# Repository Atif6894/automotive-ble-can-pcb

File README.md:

# Automotive BLE-to-CAN Communication Module

A small 4-layer board that sits on a vehicle's 12/24 V harness, talks CAN FD through a TCAN4550-Q1, and exposes it over Bluetooth LE through a CC2340R5-Q1. It runs from 9–36 V vehicle power with reverse-battery and load-dump protection, and rides through power loss on a 1S Li-ion backup cell. This is a **pre-fabrication design**: schematic, layout and manufacturing outputs are complete and pass KiCad ERC/DRC, but no board has been built or measured yet.

| Area | Implementation |
|------|----------------|
| MCU | TI CC2340R5-Q1 (CC2340R52E0WRHBRQ1, BLE 5.3, QFN32) |
| CAN | TI TCAN4550-Q1 (CAN FD controller + transceiver) |
| Vehicle input | 9–36 V, fused, TVS-clamped, ideal-diode reverse protection |
| Intermediate rail | 6.0 V (LM5164-Q1 buck) |
| Digital rail | 3.3 V (TPS62A01-Q1), shared by MCU and TCAN VIO |
| CAN interface | CAN / CAN FD, optional split 120 Ω termination |
| MCU ↔ CAN | SPI + nINT / RST / nWKRQ |
| Backup power | 1S Li-ion connector, BQ24074 charger / power path |
| RF | TI SWRU120D inverted-F PCB antenna, U.FL conducted-test option |
| Debug | 10-pin Cortex SWD + 28 test points |
| PCB | 80 × 60 mm, 4 layers, 1.6 mm, single-sided assembly |
| EDA | KiCad 10 |

## PCB Preview

Full schematic: [schematic/schematic.pdf](schematic/schematic.pdf) · all copper layers: [schematic/pcb_layers.pdf](schematic/pcb_layers.pdf)

---

## Overview

The brief was a module that connects to a vehicle CAN bus and makes it reachable over BLE. The requirements that drove the design:

- 9–36 V vehicle input (12 V and 24 V systems), surviving reverse battery and a centrally suppressed load dump
- CAN / CAN FD using the TCAN4550, with bus protection and a termination strategy
- BLE using a CC2340-family automotive part
- A backup battery so the MCU and radio stay alive through crank and brief power loss
- SPI between the BLE MCU and the CAN controller
- Programming/debug access and test access for bring-up and production
- A layout that is DRC-clean and ready to send to a 4-layer fab

## My Role

This was my project end to end at the design-package level: system architecture, part selection against datasheets, the six-sheet hierarchical schematic, PCB placement/routing and stackup choice, test and debug access, BOM, DFMEA, power budget, validation plan, and the Gerber/drill/assembly outputs. I used AI-assisted tooling during development (including scripted generation of parts of the KiCad schematic and the routing); I directed and reviewed that work against the datasheets and the KiCad checks, and I'm responsible for the design decisions described here.

## System Architecture

Power comes in on J1 (Molex Micro-Fit 3.0, 2×3), which also carries CANH/CANL and an ignition line. The vehicle supply goes fuse → TVS → ideal diode → 6.0 V buck. The 6.0 V rail feeds the TCAN4550's VSUP directly and also feeds the BQ24074 power-path charger; the charger's output (vehicle-derived or from the battery) feeds a 3.3 V buck that powers the CC2340 and the TCAN4550's logic I/O. The CC2340 talks to the TCAN4550 over SPI0 plus interrupt, reset and wake lines. The antenna is at the top-left board edge, the vehicle connector at the bottom-right.

## Power Architecture

```
J1 VBAT 9–36 V
 └─ F1 1 A fuse ─ D1 SMDJ36CA TVS ─ U1 LM74700-Q1 + Q1 BUK7Y41-80E (ideal diode)
     └─ VIN_PROT (33 µF/50 V bulk)
         └─ U2 LM5164-Q1 buck, ~300 kHz, UVLO 7.5 V / 7.0 V ──► V6P0 = 6.0 V
             ├─ FB1 ─► TCAN4550 VSUP
             └─ U3 BQ24074 IN ──► VBATSYS (4.4 V, or battery) ◄─► J3 1S Li-ion
                   └─ U4 TPS62A01-Q1 ──► +3V3 (3.32 V) ─► CC2340 VDDS, TCAN VIO
```

- **Reverse polarity:** an LM74700-Q1 driving an 80 V N-FET instead of a series Schottky. It blocks a reversed battery (to −36 V) without the ~0.5 V forward drop and heat of a diode. I picked the BUK7Y41-80E (standard-level) over the logic-level BUK9Y41 because the logic-level part's V<sub>GS</sub> rating doesn't cover the controller's gate drive.
- **Transients:** the SMDJ36CA (V<sub>RWM</sub> 36 V, V<sub>C</sub> ≤ 58.1 V) sits right after the fuse. The design assumes the vehicle has central load-dump suppression (ISO 16750-2 test B), so the clamped node stays inside the LM74700 (65 V abs), FET (80 V) and LM5164 (100 V) ratings.
- **Buck:** the LM5164-Q1 handles the full input range with margin; its UVLO divider (7.5 V rising / 7.0 V falling) cleanly hands over to the battery during cranking instead of letting the rail droop.
- **High-voltage nets** (VIN_RAW/FUSED/PROT, SW, gate) are in their own net class with 0.3 mm clearance.

Full set-point math, load budget and calculated thermal numbers are in [documentation/POWER_BUDGET.md](documentation/POWER_BUDGET.md).

## CAN / CAN FD

- **TCAN4550-Q1** integrates the CAN FD controller and transceiver, so the CC2340 (which has no CAN peripheral) only needs SPI: SCLK DIO8, CSN DIO11, POCI DIO12, PICO DIO13, plus nINT (DIO14), RST (DIO18), nWKRQ (DIO19).
- **Clock:** 40 MHz crystal with 100 Ω series on OSC1.
- **Bus protection** at the connector: PESD2CAN ESD diode, then a TDK ACT45B common-mode choke, then 47 pF line caps, then 0 Ω links (R40/R41) that can be swapped for series damping.
- **Termination:** split termination, 2 × 60.4 Ω with a 4.7 nF midpoint cap to GND, connected through solder jumpers JP1/JP2. Default open, because a plug-in module is usually a bus *tap*, not an end node. Closing both jumpers makes it a 120 Ω end node on the bench. The silkscreen says so next to the jumpers.
- **Wake:** ignition line into WAKE through the TCAN datasheet's 33 k / 3 k / 10 nF network; INH has a 100 k pull-down.
- **nWKRQ:** this pin defaults to the TCAN's internal 3.6 V rail, which is above the CC2340's 3.3 V I/O. A 1 k series resistor limits current into the MCU pin until firmware switches nWKRQ to VIO (register 0x0800 bit 19).

## BLE / MCU

- **Part:** CC2340R52E0WRHBRQ1 (CC2340R5-Q1, AEC-Q100). The brief named "CC2340R40", which I couldn't find in TI's documentation, so I used the closest automotive family member and flagged it.
- **Clocks:** 48 MHz crystal (TZ3908AAAO43, the part TI validates) and 32.768 kHz crystal for sleep timing.
- **Supply:** 100 nF per VDDS pin, internal DC/DC with 10 µH + 10 µF on VDDR as TI requires, 1 µF on VDDD.
- **RF:** LPF → DC block → π-match → 0.40 mm 50 Ω microstrip → TI SWRU120D inverted-F antenna at the board edge, with a copper keep-out on all four layers. Matching values are TI reference starting values, not tuned.
- **Debug:** SWDIO DIO16, SWDCK DIO17, nRESET to the SWD header.

## Backup Battery

J3 is a keyed JST PH 3-pin (BAT+, NTC, GND) for a protected 1S Li-ion pack with a 10 k NTC. The BQ24074 charges at 100 mA (R<sub>ISET</sub> 8.87 k) with a ~0.5 A input limit, and its power-path output switches from the 6.0 V input to the battery when vehicle power drops. Intended behavior during crank or power loss: the CC2340 and radio stay up on the battery, the TCAN4550 loses VSUP and has to be re-initialized by firmware when power returns. That behavior is designed from the datasheets, **not** tested.

## PCB Layout

| Top 3D | Bottom 3D |
|---|---|
|  |  |

| L1 F.Cu | L2 In1 (GND) | L3 In2 | L4 B.Cu |
|---|---|---|---|
|  |  |  |  |

- **Stackup:** F.Cu signals + RF / In1 solid GND / In2 signals + power / B.Cu routing, GND pours on all layers. Assumes a JLC04161H-7628 style stackup (0.21 mm prepreg to In1), which sets the 0.40 mm microstrip width. Details: [documentation/STACKUP_AND_LAYOUT.md](documentation/STACKUP_AND_LAYOUT.md).
- **Zoning:** antenna top-left with keep-out; CC2340 just below it with the RF chain in a straight line to the feed; power input on the right edge (fuse, TVS, ideal diode in a row) with the buck top-right and a tight CIN–U2–L1–COUT loop; vehicle connector J1 bottom-right with CAN ESD and CMC directly next to it; TCAN4550 between J1 and the MCU to keep SPI short; battery connector bottom-left, away from the antenna.
- **Ground:** every GND pad gets a via to In1, via arrays under the thermal pads, four plated M3 holes tied to GND.
- **Assembly:** all parts on the top side, 3 fiducials, single reflow pass.

## Design Highlight: one 6.0 V rail doing three jobs

**Problem.** The TCAN4550 needs VSUP ≥ 5.5 V. Its internal LDO burns (VSUP − 5 V) × ~80 mA whenever the bus is driven, so feeding it straight from a 24–36 V vehicle input would dissipate a lot of heat in a small QFN (the datasheet's thermal-shutdown example is at 20 V). Meanwhile, the BLE side needs a battery-backed 3.3 V rail, and the charger that provides it has its own input window (BQ24074 OVP at 10.5 V).

**Obvious alternatives.** Run VSUP from the protected vehicle rail (simple, hot at 24 V+), or build a 5 V rail (below TCAN's 5.5 V minimum), or add a separate rail for the charger.

**What I did.** One LM5164 buck set to 6.0 V (1.2 V × (1 + 200 k / 49.9 k) = 6.01 V). That single number satisfies three constraints at once:

1. above TCAN VSUP minimum (5.5 V) with margin for tolerance and the FB1 ferrite drop,
2. low enough that the TCAN's internal LDO dissipates roughly 1 V × load rather than 20–30 V × load,
3. inside the BQ24074's input range, so the same rail also feeds the charger/power path, which then makes the 3.3 V rail for the MCU **and** the TCAN VIO pin.

**Payoff.** Both chips share one 3.3 V logic domain, so SPI/interrupt/reset need no level shifters. The CAN transceiver's heat is decoupled from the vehicle voltage. The battery path only has to back up the low-power 3.3 V domain, while the power-hungry CAN supply simply drops out during a crank and gets re-initialized, which is fine for a bus tap. It's one regulator and two resistors, instead of a 5 V rail plus a separate charger supply plus level translation.

A smaller detail in the same spirit: the IFA antenna's two grounded shorting tabs are connected through 0 Ω links (R67/R68), and the feed has a 0 Ω steering pair (R65 fitted / R66 DNP) to a U.FL connector. That makes the antenna's DC short and the conducted-RF path reconfigurable with a soldering iron during RF tuning, without a board respin.

## Design Verification (in KiCad, not on hardware)

Run with KiCad 10.0.6 `kicad-cli` on the delivered files ([reports](manufacturing/reports/)):

- **ERC:** 0 errors, 0 warnings.
- **DRC:** 0 errors, 0 unconnected items, 0 schematic-parity issues. 45 warnings remain:
  - 23 `via_dangling`: vias connected on only one layer (including some on signal nets such as SPI_nCS, nRESET, X32P, VBATSYS left over from routing). They don't break connectivity but should be cleaned up before fab.
  - 2 `hole_to_hole`: these are routing vias, not mounting holes or intentional mechanical features. Two GND vias at (52.5, 60.1) / (52.6, 59.8) mm have only 0.078 mm drill-to-drill spacing, and two TCAN_GPO2 vias at (56.8, 75.0) / (57.2, 75.1) mm have 0.193 mm, against a 0.2 mm rule. Each pair is on the same net, so there's no electrical short, but the 0.078 mm pair is a real fabrication risk (drill breakout). **Fix before ordering** by deleting or moving one via of each pair.
  - 20 silkscreen overlap / silk-over-copper from stock footprint outlines.
- The copper-zone fill saved in the board file was stale: run without refilling zones, DRC flags two IGN_RAW tracks touching the B.Cu GND pour. I refilled the zones (no tracks, footprints or nets changed), re-ran DRC, and regenerated the Gerbers, drill and assembly outputs from the refilled board, so the fab files match the clean DRC result.
- Symbol-pin vs footprint-pad check and BOM-vs-netlist cross-check (all references match).
- Pinouts and key values traced to datasheets: [documentation/DATASHEET_TRACE.md](documentation/DATASHEET_TRACE.md).

## Manufacturing Outputs

| File | Content |
|---|---|
| [manufacturing/gerbers.zip](manufacturing/gerbers.zip) | 4 copper layers, mask, paste, silkscreen, edge cuts, Gerber job file |
| [manufacturing/drill_files.zip](manufacturing/drill_files.zip) | Excellon drill + drill map |
| [bytebeam_pos_front.csv](manufacturing/assembly_outputs/bytebeam_pos_front.csv) | pick-and-place (top side) |
| [bytebeam.d356](manufacturing/assembly_outputs/bytebeam.d356) | IPC-D-356 netlist for bare-board test |
| [bytebeam_ipc2581.xml](manufacturing/assembly_outputs/bytebeam_ipc2581.xml) | IPC-2581 |
| [bytebeam_netlist.xml](manufacturing/assembly_outputs/bytebeam_netlist.xml) | KiCad netlist |
| [bytebeam.step](manufacturing/assembly_outputs/bytebeam.step) | 3D STEP model (a few connector/fuse 3D models were missing at export) |
| [documentation/BOM.csv](documentation/BOM.csv) | BOM with MPN, ratings, AEC qualification, alternatives, open assumptions |
| [schematic/assembly_top.pdf](schematic/assembly_top.pdf) | top assembly drawing |

## Debug / Bring-Up Considerations

I laid out the test access in the order I'd bring the board up:

1. **Power, stage by stage, with a current-limited supply.** Test points on every rail along the chain: VIN_RAW (TP1) → VIN_FUSED (TP2) → VIN_PROT (TP3) → V6P0 (TP4/TP25) → VBAT (TP5) / VBATSYS (TP6) → +3V3 (TP8/TP19), plus BQ_PGOOD (TP26) and BQ_nCHG (TP7). If a rail is missing, the fault is between two adjacent test points. Five GND test points spread over the board for scope grounds.
2. **MCU alive.** 10-pin Cortex SWD header (J2) for an XDS110/J-Link, and SWDIO/SWDCK/nRESET are also on test pads (TP16/TP17/TP15) for a pogo-pin fixture in production. A blinky LED is on a DIO.
3. **SPI to the TCAN.** SCLK, MOSI, MISO, nCS, nINT and TCAN_RST all on test points (TP21/22/12/23/20/24), so a logic analyzer can decode the first device-ID read (registers 0x0000–0x0003) without probing a 0.5 mm QFN.
4. **CAN.** CANH/CANL test points (TP9/TP10), TCAN_INH (TP11), and the termination jumpers so the board can be an end node on a two-node bench bus.
5. **RF.** Fit R66 / remove R65 to route the radio to the U.FL connector (J4) for conducted power and harmonics on a spectrum analyzer, then reverse it for antenna S11 on a VNA.

Full step-by-step plan: [documentation/VALIDATION_PLAN.md](documentation/VALIDATION_PLAN.md).

## What Still Needs Physical Validation

Nothing has been fabricated, powered or measured. All of the following are open:

- Fix the two `hole_to_hole` via pairs and clean up the dangling vias before fab
- RF matching network tuning (values are TI reference starting points; topology needs confirming against the LP-EM-CC2340R5-Q1 design files)
- Antenna performance on this stackup and in an enclosure (S11, efficiency, range)
- 50 Ω microstrip impedance with the fab's real dielectric data
- Crystal load values (TCAN 40 MHz caps are assumptions)
- EMC/EMI (CISPR 25; the 300 kHz buck lands in the AM band), ESD (IEC 61000-4-2 / ISO 10605)
- Transients: ISO 7637-2 pulses, ISO 16750-2 load dump, reverse battery, cranking profile
- Thermal performance (current numbers are datasheet θ<sub>JA</sub> estimates)
- CAN signal integrity and FD bit timing (CANH/CANL are routed as two nets, not a coupled pair)
- Battery charging, power-path handover and sleep current
- Land patterns for Coilcraft XGL inductors and the 48 MHz crystal against vendor drawings
- BQ24074 is not AEC-Q100 qualified; an automotive-qualified charger would be needed for production
- Board bring-up and firmware

Design risks and mitigations are tracked in the [DFMEA](documentation/DFMEA.csv) (33 failure modes).

## Design Files

- Schematic: [schematic/schematic.pdf](schematic/schematic.pdf) and per-sheet images in [images/](images/)
- PCB layer plots: [schematic/pcb_layers.pdf](schematic/pcb_layers.pdf)
- KiCad project: [design_files/](design_files/) (open `bytebeam_ble_can.kicad_pro` in KiCad 10; custom symbols/footprints in `design_files/lib/`)
- BOM: [documentation/BOM.csv](documentation/BOM.csv)
- DFMEA: [documentation/DFMEA.csv](documentation/DFMEA.csv)
- Power budget: [documentation/POWER_BUDGET.md](documentation/POWER_BUDGET.md)
- Stackup and layout notes: [documentation/STACKUP_AND_LAYOUT.md](documentation/STACKUP_AND_LAYOUT.md)
- Validation plan: [documentation/VALIDATION_PLAN.md](documentation/VALIDATION_PLAN.md)
- Manufacturing outputs: [manufacturing/](manufacturing/)

Originally done as a hardware design assignment for Bytebeam; the board silkscreen still carries that name.

## Tools and Skills

KiCad 10 (schematic capture, 4-layer PCB layout, DRC/ERC, fab outputs) · automotive power electronics (protection, buck regulation, power path) · CAN / CAN FD · SPI · BLE · RF layout · DFMEA · Python for calculations and output generation

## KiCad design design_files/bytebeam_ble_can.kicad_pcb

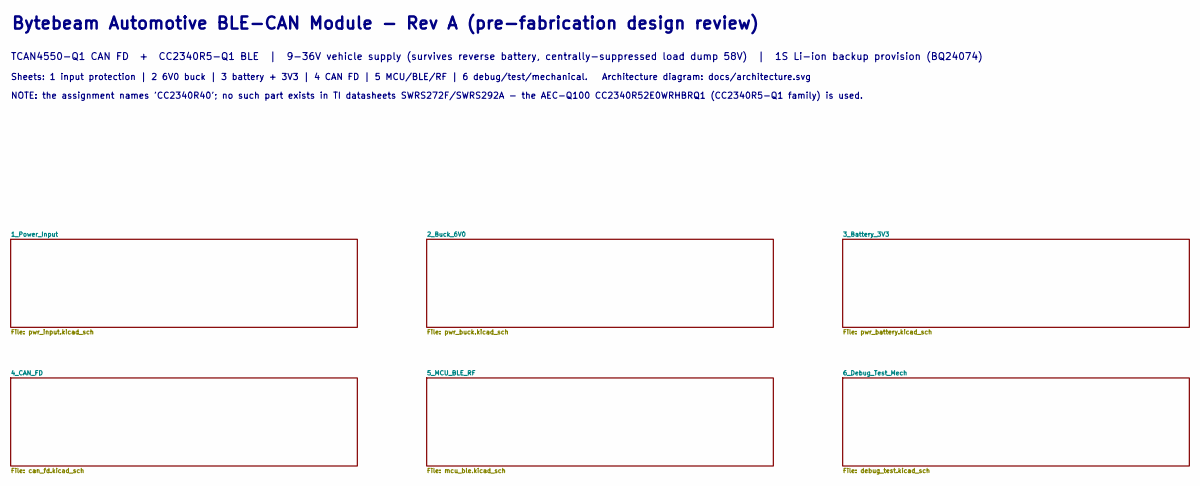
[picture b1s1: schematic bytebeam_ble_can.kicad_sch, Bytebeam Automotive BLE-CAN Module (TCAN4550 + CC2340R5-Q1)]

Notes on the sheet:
Sheets: 1 input protection | 2 6V0 buck | 3 battery + 3V3 | 4 CAN FD | 5 MCU/BLE/RF | 6 debug/test/mechanical. Architecture diagram: docs/architecture.svg
Bytebeam Automotive BLE-CAN Module - Rev A (pre-fabrication design review)
NOTE: the assignment names 'CC2340R40'; no such part exists in TI datasheets SWRS272F/SWRS292A - the AEC-Q100 CC2340R52E0WRHBRQ1 (CC2340R5-Q1 family) is used.
TCAN4550-Q1 CAN FD + CC2340R5-Q1 BLE | 9-36V vehicle supply (survives reverse battery, centrally-suppressed load dump 58V) | 1S Li-ion backup provision (BQ24074)

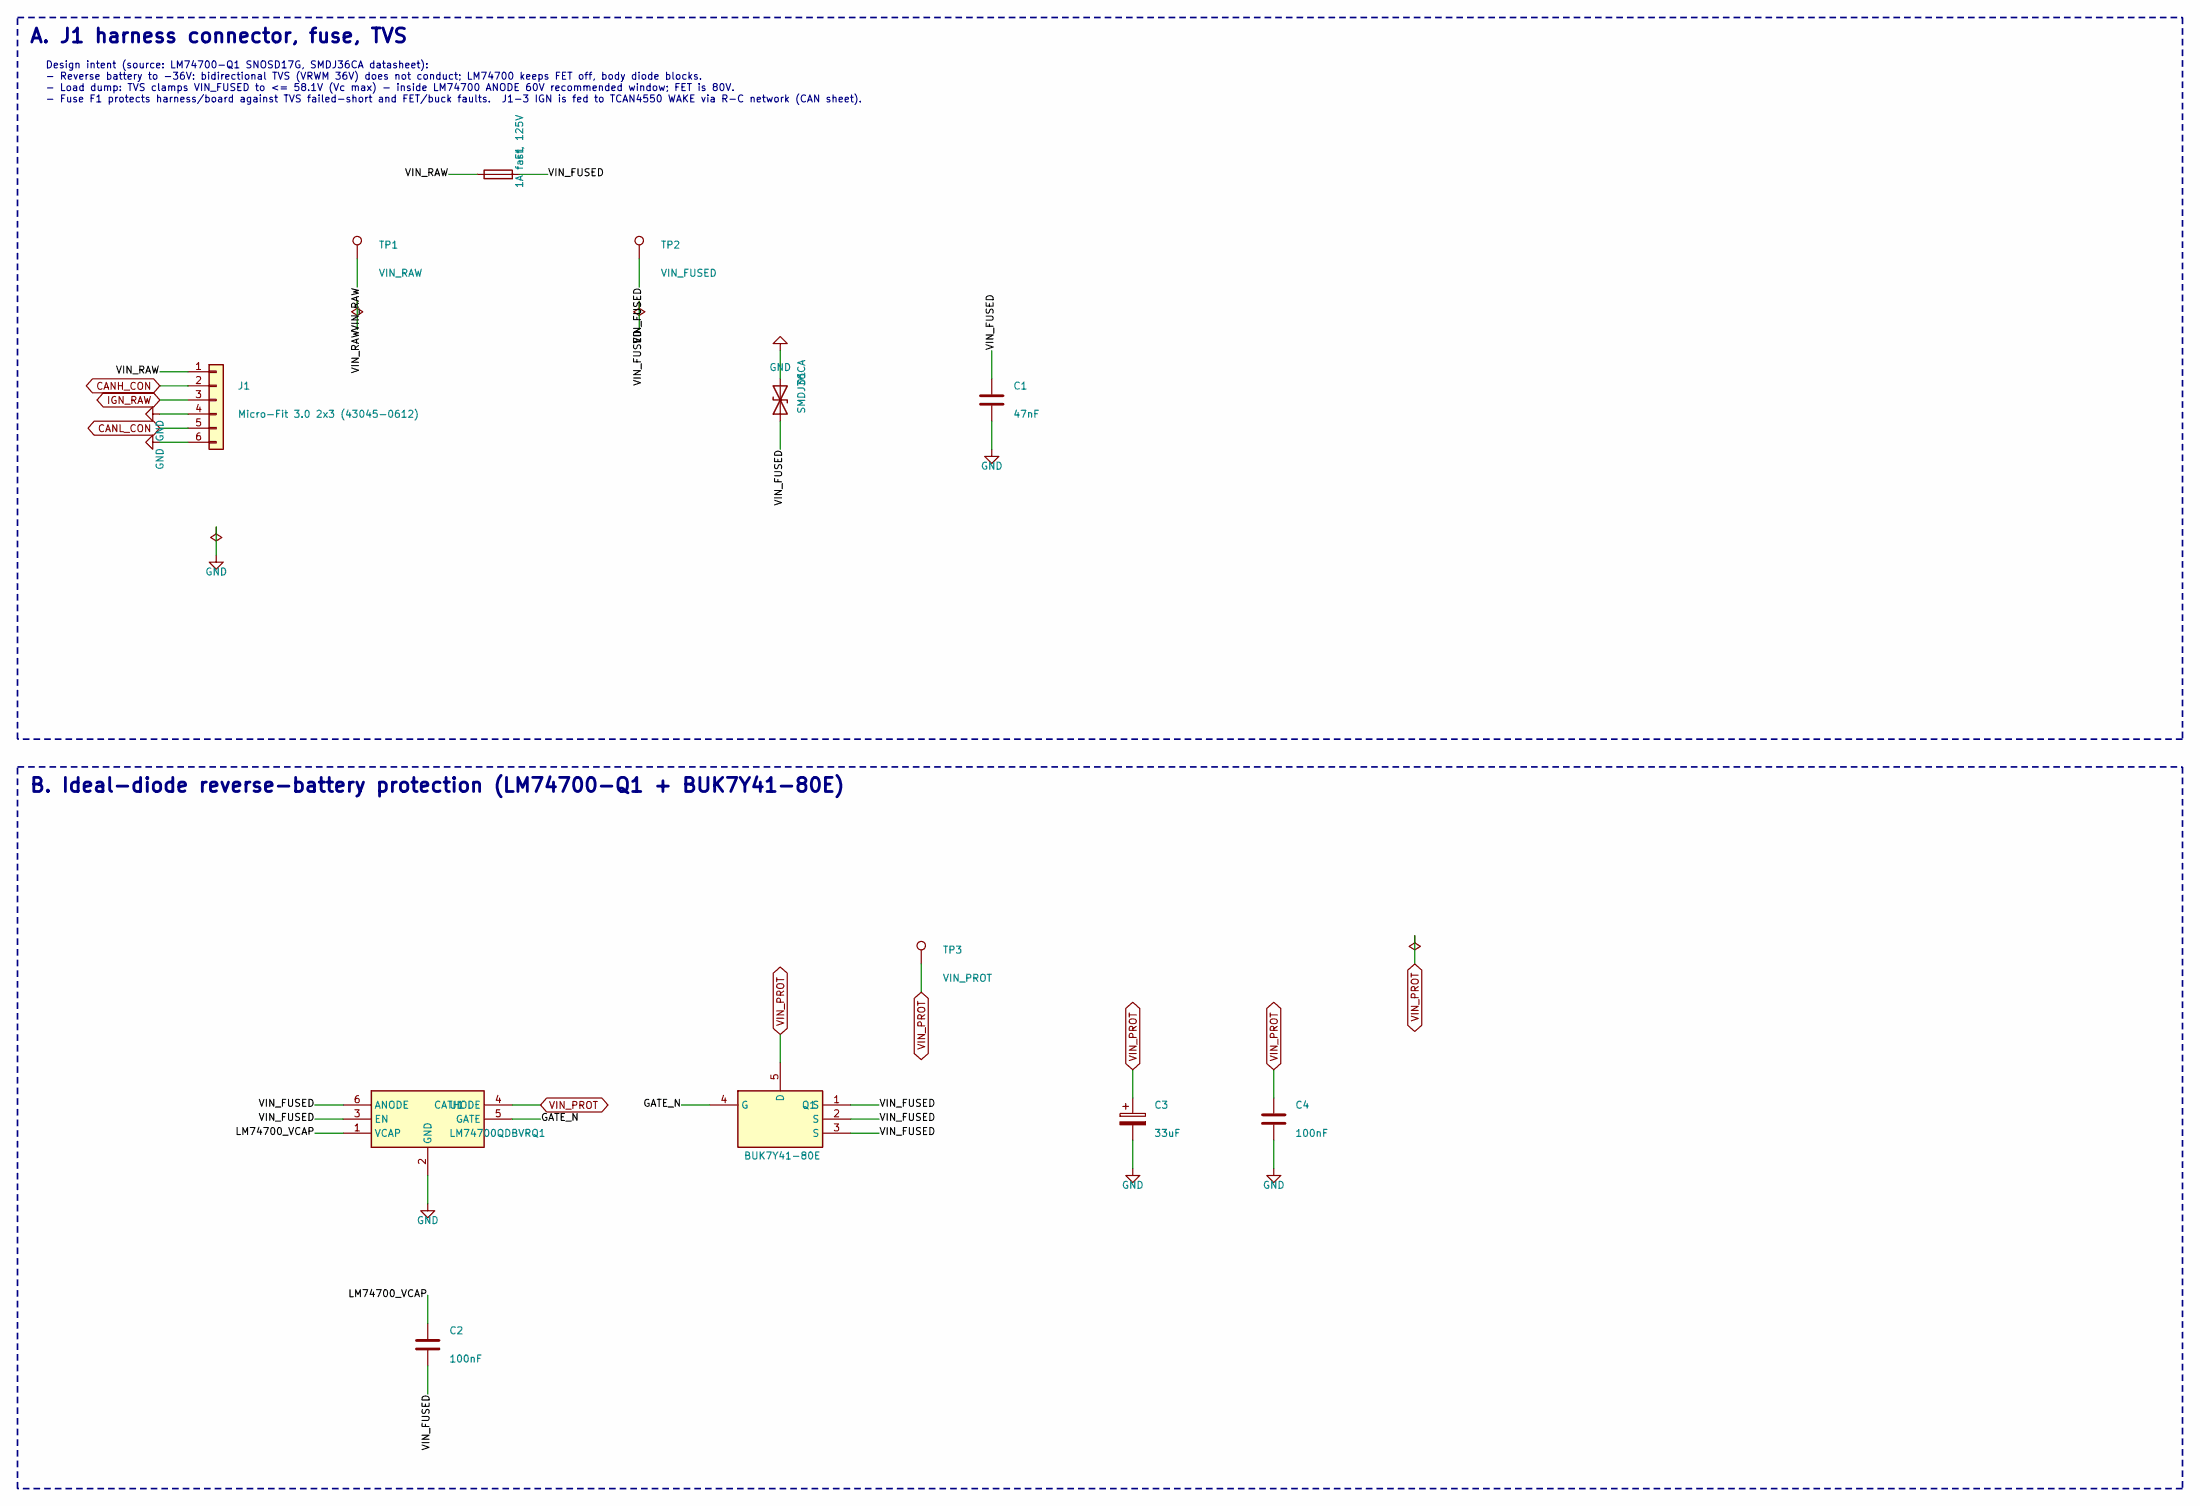
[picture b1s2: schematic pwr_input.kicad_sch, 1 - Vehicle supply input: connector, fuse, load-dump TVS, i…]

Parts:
C1: 47nF; C_0603_1608Metric; Rating 100V X7R; MPN GCM-series (AEC-Q200) 47nF 100V X7R
C2: 100nF; C_0603_1608Metric; Rating 25V X7R; MPN GCM-series (AEC-Q200) 100nF 25V X7R
C3: 33uF; CP_Elec_6.3x5.8; Rating 50V X7R; MPN EEE-FN1H330P
C4: 100nF; C_0603_1608Metric; Rating 100V X7R; MPN GCM-series (AEC-Q200) 100nF 100V X7R
D1: SMDJ36CA; D_SMC; Rating 3000W bidirectional, VRWM 36V, Vc(max) 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; MPN SMDJ36CA
F1: 1A fast, 125V; Fuse_Littelfuse-NANO2-451_453; Rating 1A, 125V, very-fast-acting NANO2 (sourc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; MPN 0451001.MRL
J1: Micro-Fit 3.0 2x3 (43045-0612); Molex_Micro-Fit_3.0_43045-0612_2x03_P3.00mm_Vertical; Rating Micro-Fit 3.0 2x3 vertical THT, 5A/circ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; MPN 43045-0612
Q1: BUK7Y41-80E; LFPAK56; Rating 80V 41mOhm std-level, VGS +/-20V (LM747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; MPN BUK7Y41-80E,115
TP1: VIN_RAW; TestPoint_Pad_D1.5mm; Rating bare copper pad; MPN PCB test pad D1.5mm
TP2: VIN_FUSED; TestPoint_Pad_D1.5mm; Rating bare copper pad; MPN PCB test pad D1.5mm
TP3: VIN_PROT; TestPoint_Pad_D1.5mm; Rating bare copper pad; MPN PCB test pad D1.5mm
U1: LM74700QDBVRQ1; SOT-23-6; Rating ANODE +/-60V rec. (65V abs), AEC-Q100 g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; MPN LM74700QDBVRQ1

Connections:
/1_Power_Input/GATE_N: Q1.4 (G), U1.5 (GATE)
/1_Power_Input/LM74700_VCAP: C2.1, U1.1 (VCAP)
/1_Power_Input/VIN_FUSED: C1.1, C2.2, D1.1 (A1), F1.2, Q1.1 (S), Q1.2 (S), Q1.3 (S), TP2.1, U1.3 (EN), U1.6 (ANODE)
/1_Power_Input/VIN_RAW: F1.1, J1.1, TP1.1
CANH_CON: J1.2; also elsewhere on the board
CANL_CON: J1.5; also elsewhere on the board
GND: C1.2, C3.2, C4.2, D1.2 (A2), J1.4, J1.6, U1.2 (GND); also elsewhere on the board
IGN_RAW: J1.3; also elsewhere on the board
VIN_PROT: C3.1, C4.1, Q1.5 (D), TP3.1, U1.4 (CATHODE); also elsewhere on the board

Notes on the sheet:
B. Ideal-diode reverse-battery protection (LM74700-Q1 + BUK7Y41-80E)
Design intent (source: LM74700-Q1 SNOSD17G, SMDJ36CA datasheet): - Reverse battery to -36V: bidirectional TVS (VRWM 36V) does not conduct; LM74700 keeps FET off, body diode blocks. - Load dump: TVS clamps VIN_FUSED to <= 58.1V (Vc max) - inside LM74700 ANODE 60V recommended window; FET is 80V. - Fu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
A. J1 harness connector, fuse, TVS

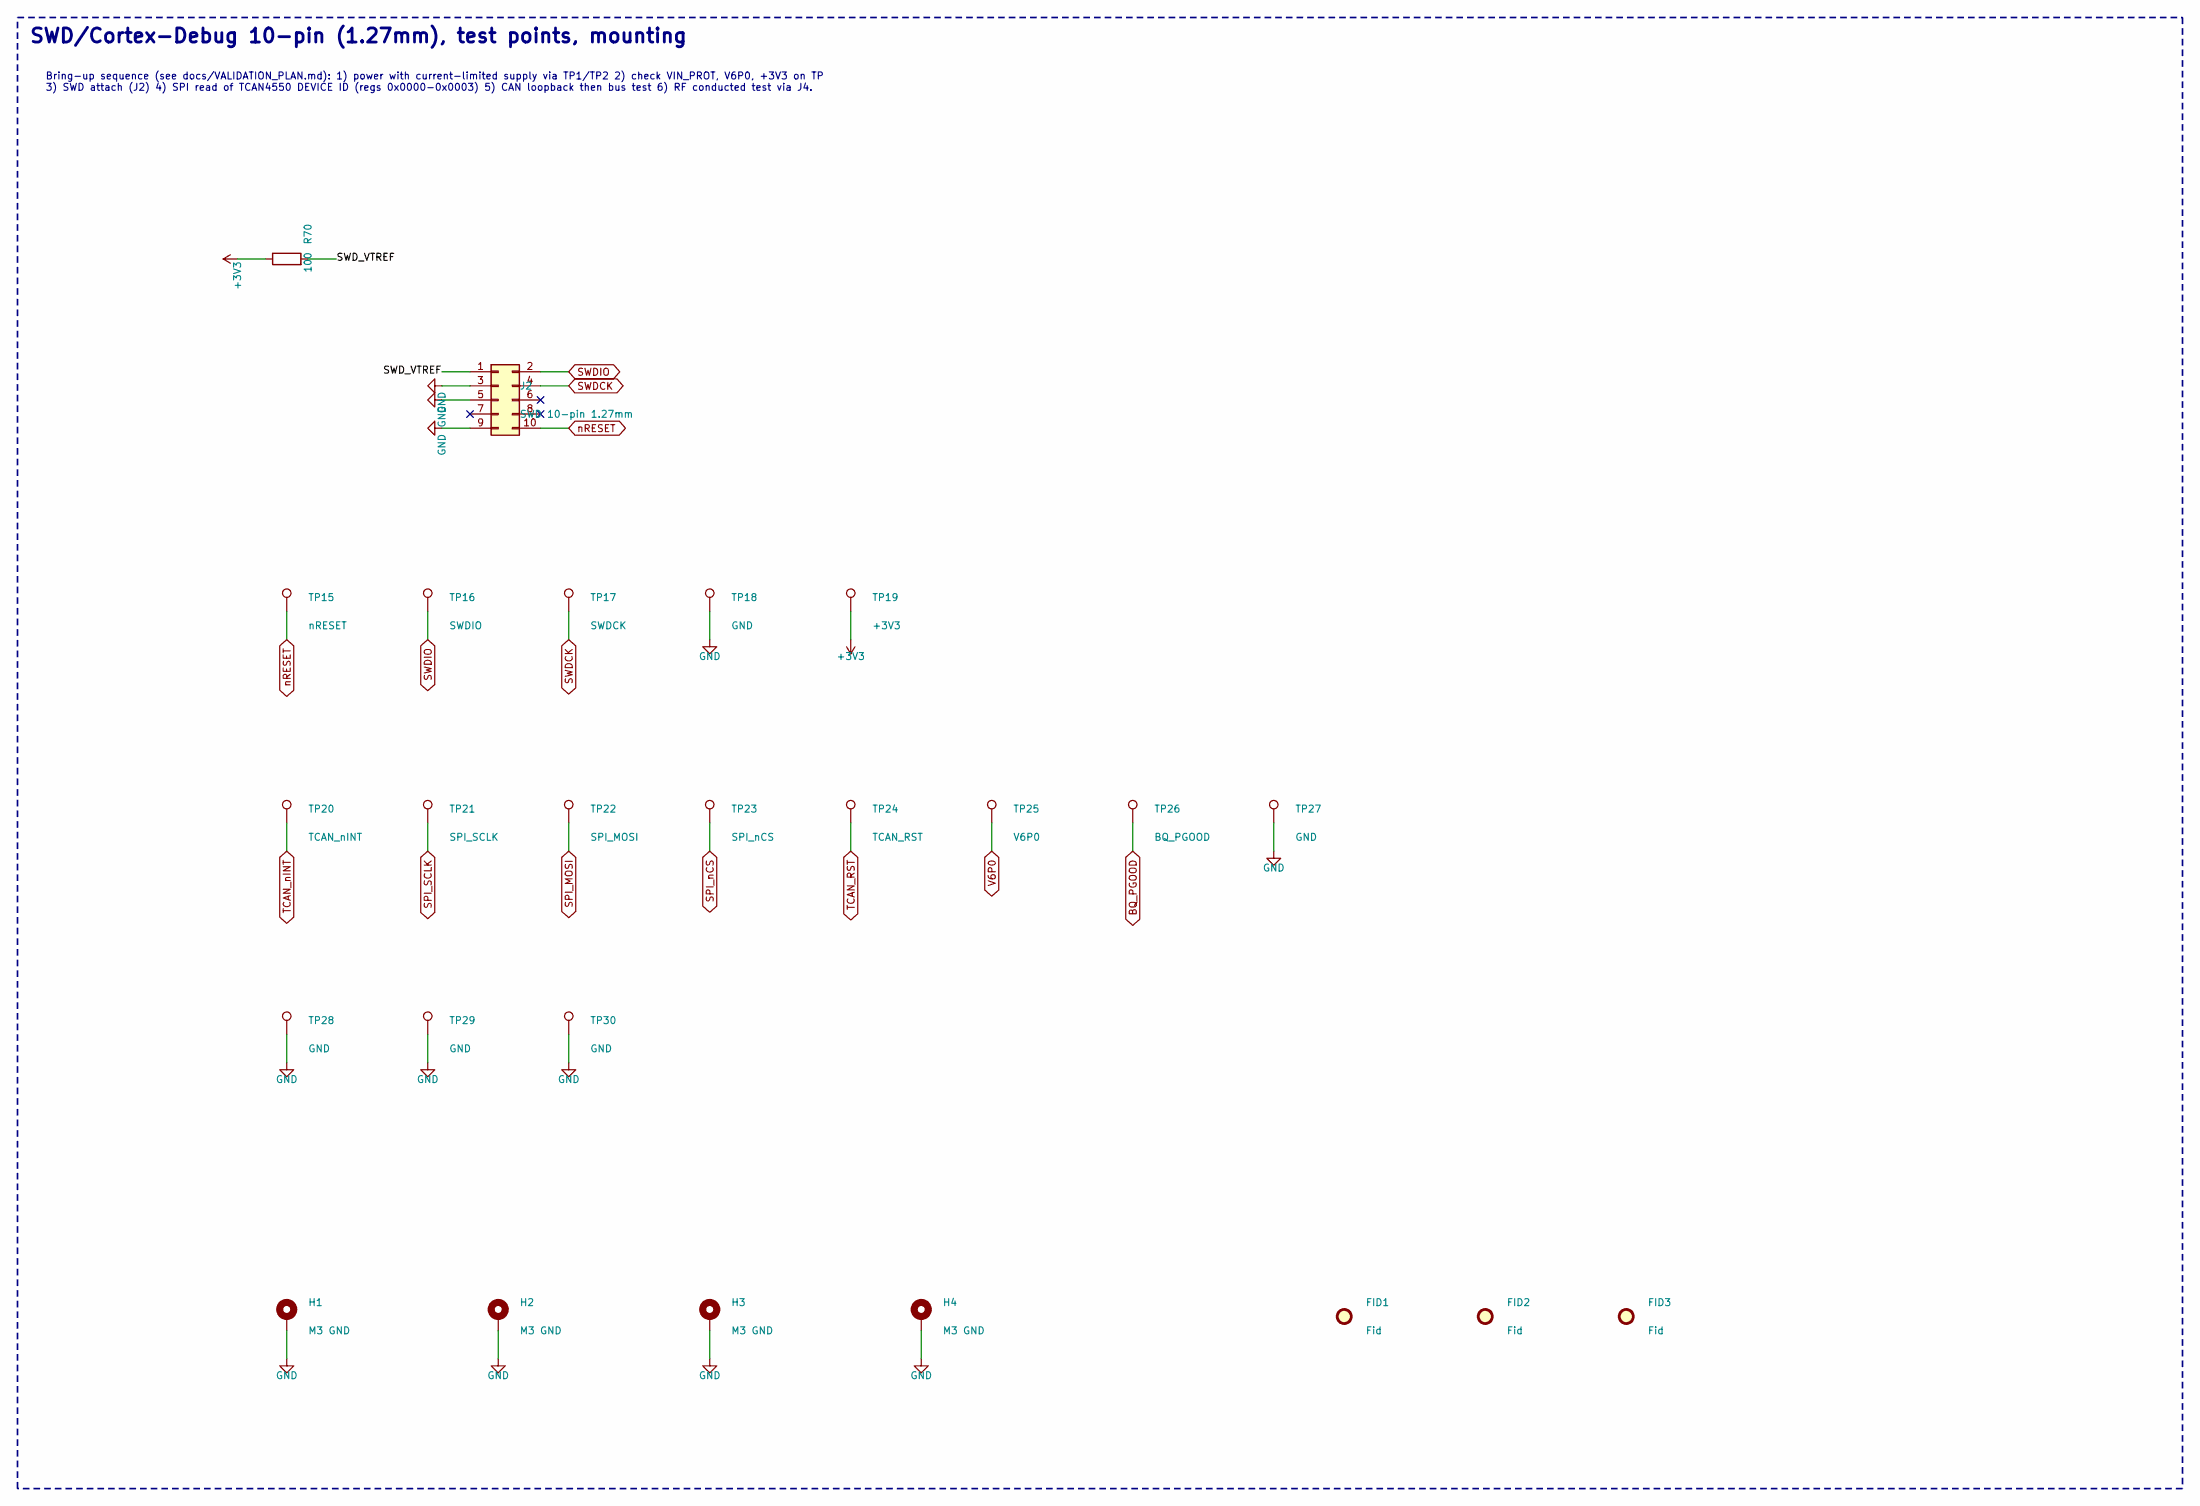
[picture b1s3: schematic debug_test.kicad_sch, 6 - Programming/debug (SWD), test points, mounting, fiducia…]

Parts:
FID1, FID2, FID3: Fid; Fiducial_1mm_Mask2mm; Rating n/a; MPN Fiducial 1mm
H1, H2, H3, H4: M3 GND; MountingHole_3.2mm_M3_Pad_Via; Rating 3.2mm, plated, GND; MPN M3 plated hole
J2: SWD 10-pin 1.27mm; PinHeader_2x05_P1.27mm_Vertical_SMD; Rating 2x5 1.27mm SMD shrouded, ARM Cortex Deb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; MPN FTSH-105-01-L-DV-K
R70: 100; R_0402_1005Metric; Rating 1%, AEC-Q200 thick film; MPN AC0402FR-07100RL
TP15: nRESET; TestPoint_Pad_D1.5mm; Rating bare copper pad; MPN PCB test pad D1.5mm
TP16: SWDIO; TestPoint_Pad_D1.5mm; Rating bare copper pad; MPN PCB test pad D1.5mm
TP17: SWDCK; TestPoint_Pad_D1.5mm; Rating bare copper pad; MPN PCB test pad D1.5mm
TP18, TP27, TP28, TP29, TP30: GND; TestPoint_Pad_D1.5mm; Rating bare copper pad; MPN PCB test pad D1.5mm
TP19: +3V3; TestPoint_Pad_D1.5mm; Rating bare copper pad; MPN PCB test pad D1.5mm
TP20: TCAN_nINT; TestPoint_Pad_D1.5mm; Rating bare copper pad; MPN PCB test pad D1.5mm
TP21: SPI_SCLK; TestPoint_Pad_D1.5mm; Rating bare copper pad; MPN PCB test pad D1.5mm
TP22: SPI_MOSI; TestPoint_Pad_D1.5mm; Rating bare copper pad; MPN PCB test pad D1.5mm
TP23: SPI_nCS; TestPoint_Pad_D1.5mm; Rating bare copper pad; MPN PCB test pad D1.5mm
TP24: TCAN_RST; TestPoint_Pad_D1.5mm; Rating bare copper pad; MPN PCB test pad D1.5mm
TP25: V6P0; TestPoint_Pad_D1.5mm; Rating bare copper pad; MPN PCB test pad D1.5mm
TP26: BQ_PGOOD; TestPoint_Pad_D1.5mm; Rating bare copper pad; MPN PCB test pad D1.5mm

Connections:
+3V3: R70.1, TP19.1; also elsewhere on the board
/6_Debug_Test_Mech/SWD_VTREF: J2.1, R70.2
BQ_PGOOD: TP26.1; also elsewhere on the board
GND: H1.1, H2.1, H3.1, H4.1, J2.3, J2.5, J2.9, TP18.1, TP27.1, TP28.1, TP29.1, TP30.1; also elsewhere on the board
SPI_MOSI: TP22.1; also elsewhere on the board
SPI_SCLK: TP21.1; also elsewhere on the board
SPI_nCS: TP23.1; also elsewhere on the board
SWDCK: J2.4, TP17.1; also elsewhere on the board
SWDIO: J2.2, TP16.1; also elsewhere on the board
TCAN_RST: TP24.1; also elsewhere on the board
TCAN_nINT: TP20.1; also elsewhere on the board
V6P0: TP25.1; also elsewhere on the board
nRESET: J2.10, TP15.1; also elsewhere on the board

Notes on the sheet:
Bring-up sequence (see docs/VALIDATION_PLAN.md): 1) power with current-limited supply via TP1/TP2 2) check VIN_PROT, V6P0, +3V3 on TP 3) SWD attach (J2) 4) SPI read of TCAN4550 DEVICE ID (regs 0x0000-0x0003) 5) CAN loopback then bus test 6) RF conducted test via J4.
SWD/Cortex-Debug 10-pin (1.27mm), test points, mounting

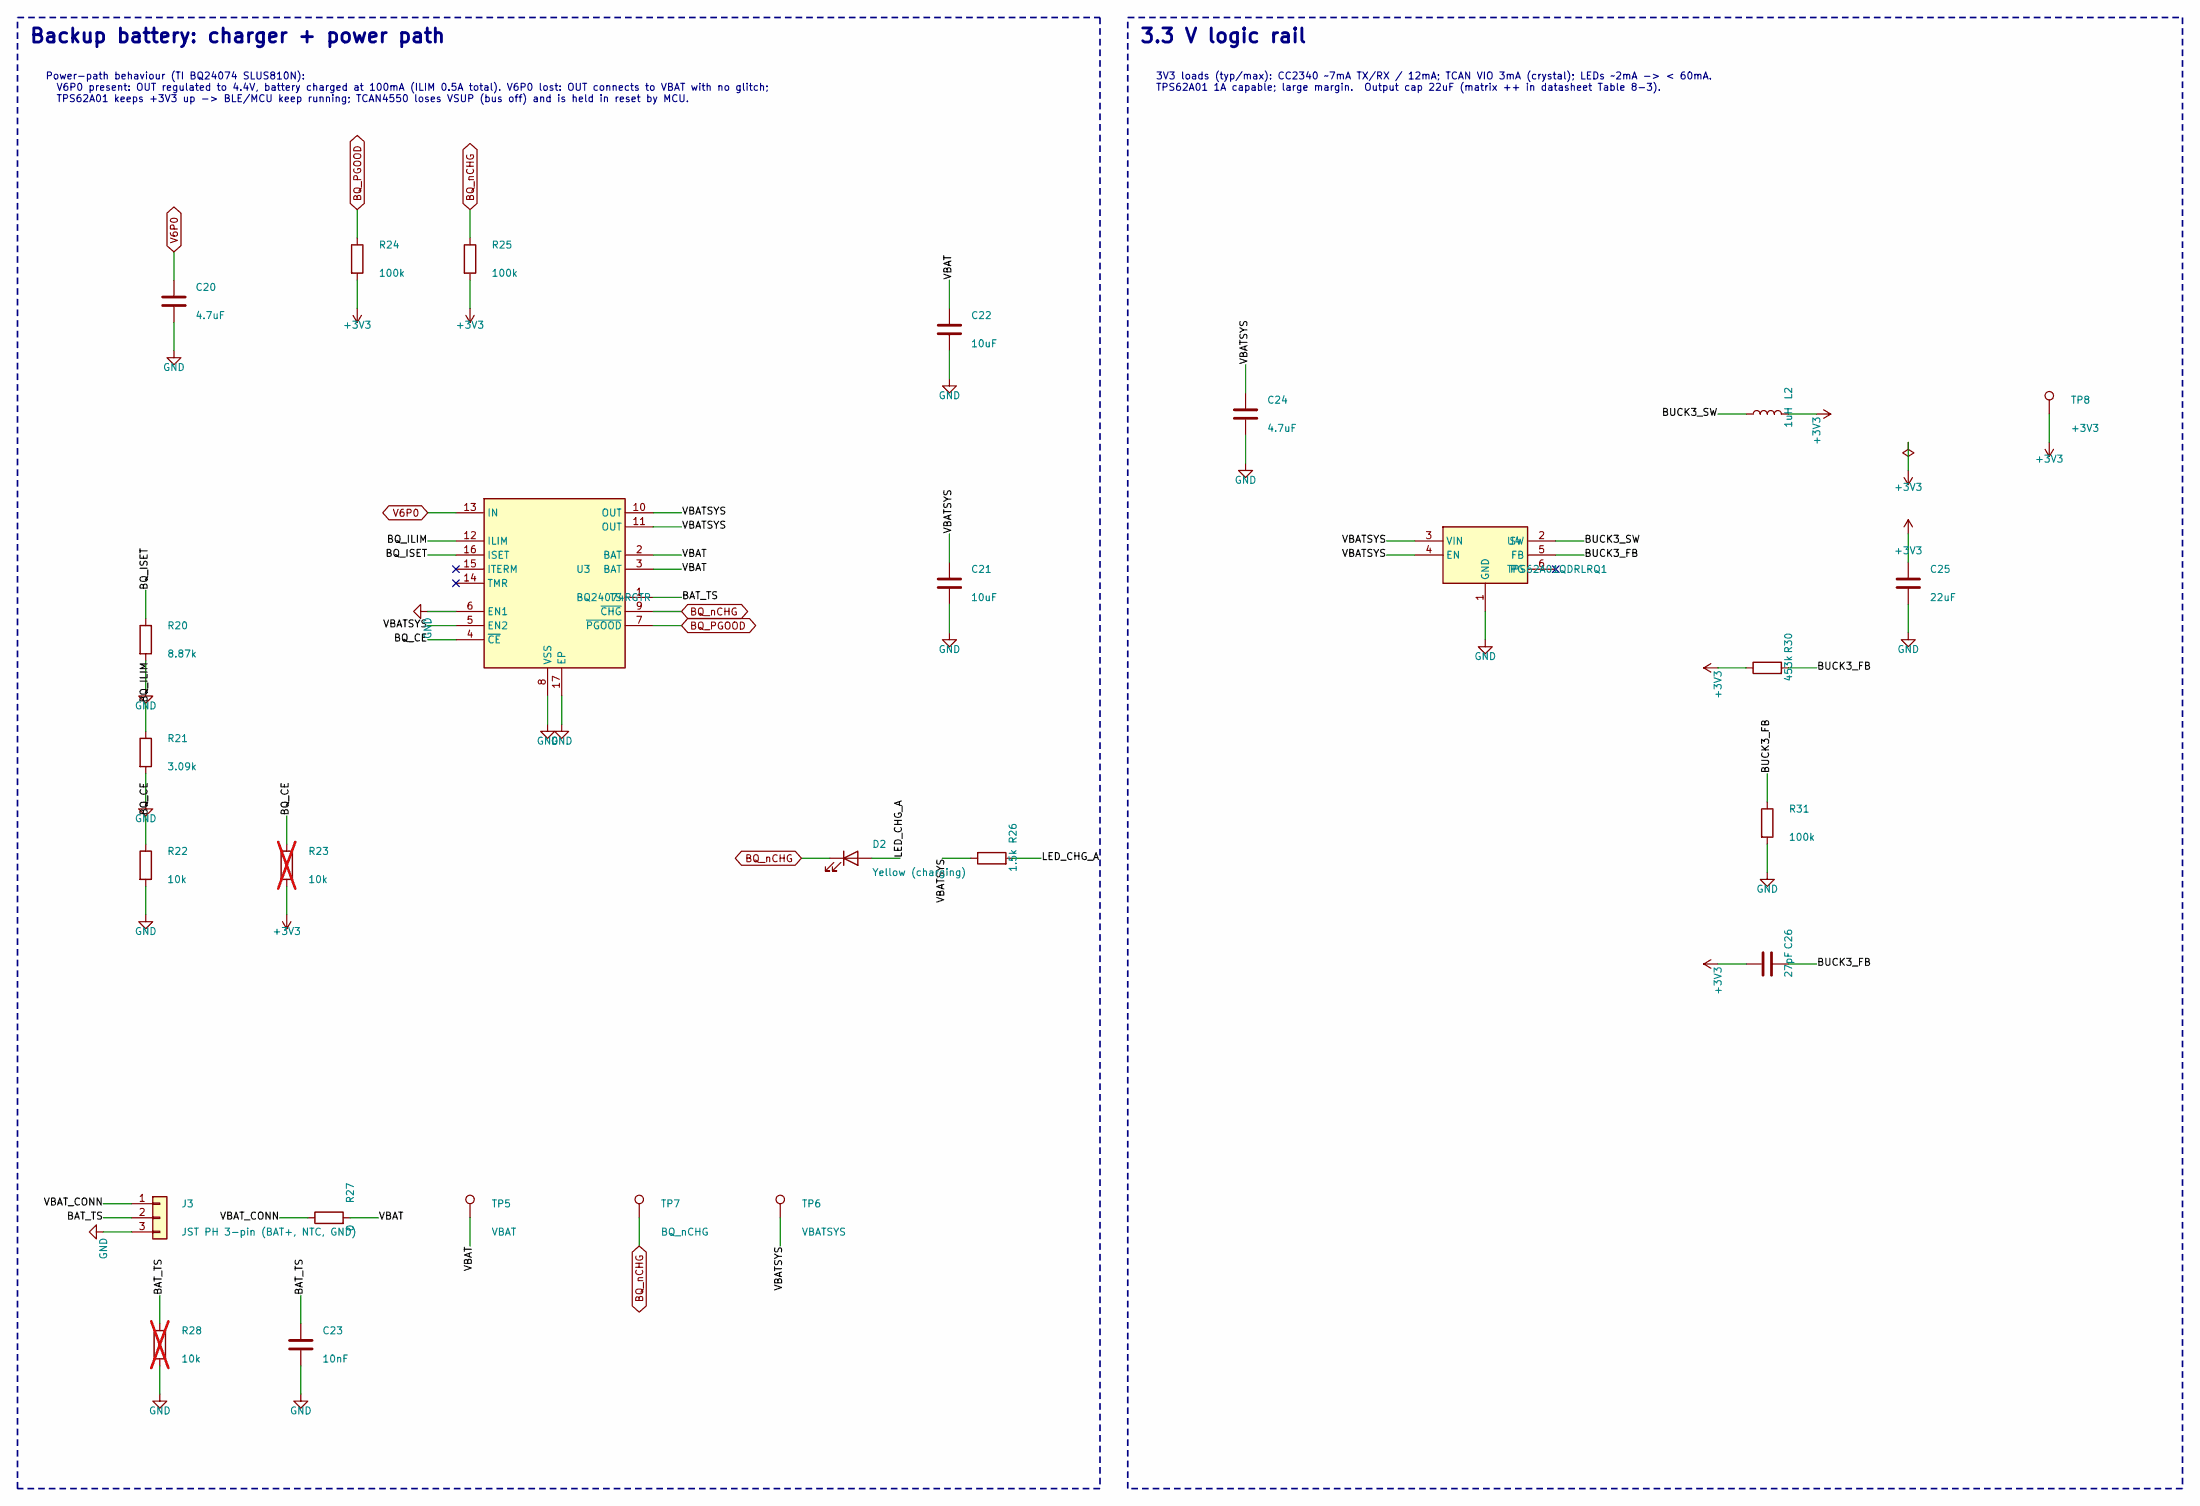
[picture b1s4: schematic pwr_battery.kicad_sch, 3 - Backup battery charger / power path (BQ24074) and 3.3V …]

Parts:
C20: 4.7uF; C_0805_2012Metric; Rating 16V X7R; MPN GCM-series (AEC-Q200) 4.7uF 16V X7R
C21, C22: 10uF; C_0805_2012Metric; Rating 10V X7R; MPN GCM-series (AEC-Q200) 10uF 10V X7R
C23: 10nF; C_0402_1005Metric; Rating 16V X7R; MPN GCM-series (AEC-Q200) 10nF 16V X7R
C24: 4.7uF; C_0805_2012Metric; Rating 10V X7R; MPN GRM21BR71A475KA73L
C25: 22uF; C_0805_2012Metric; Rating 10V X7R; MPN GRM21BZ71A226KE15L
C26: 27pF; C_0402_1005Metric; Rating 50V C0G; MPN GCM-series (AEC-Q200) 27pF 50V C0G
D2: Yellow (charging); LED_0603_1608Metric; Rating 0603 yellow, AEC-Q101 variant to select; MPN LTST-C193KSKT-5A
J3: JST PH 3-pin (BAT+, NTC, GND); JST_PH_B3B-PH-SM4-TB_1x03-1MP_P2.00mm_Vertical; Rating 2A, keyed, -25..85C; MPN B3B-PH-SM4-TB(LF)(SN)
L2: 1uH; L_Coilcraft_XxL4020; Rating 1uH, Isat 6.3A/8.8A, DCR<=9mOhm, AEC-Q2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; MPN XGL4020-102MEC
R20: 8.87k; R_0402_1005Metric; Rating 1%, AEC-Q200 thick film; MPN AC0402FR-078K87L
R21: 3.09k; R_0402_1005Metric; Rating 1%, AEC-Q200 thick film; MPN AC0402FR-073K09L
R22: 10k; R_0402_1005Metric; Rating 1%, AEC-Q200 thick film; MPN AC0402FR-0710KL
R23, R28: 10k; R_0402_1005Metric; Rating 1%, AEC-Q200 thick film; MPN AC0402FR-0710KL; not fitted
R24, R25, R31: 100k; R_0402_1005Metric; Rating 1%, AEC-Q200 thick film; MPN AC0402FR-07100KL
R26: 1.5k; R_0402_1005Metric; Rating 1%, AEC-Q200 thick film; MPN AC0402FR-071K5L
R27: 0; R_0603_1608Metric; Rating 0R, 1A; MPN AC0603FR-070RL
R30: 453k; R_0402_1005Metric; Rating 1%, AEC-Q200 thick film; MPN AC0402FR-07453KL
TP5: VBAT; TestPoint_Pad_D1.5mm; Rating bare copper pad; MPN PCB test pad D1.5mm
TP6: VBATSYS; TestPoint_Pad_D1.5mm; Rating bare copper pad; MPN PCB test pad D1.5mm
TP7: BQ_nCHG; TestPoint_Pad_D1.5mm; Rating bare copper pad; MPN PCB test pad D1.5mm
TP8: +3V3; TestPoint_Pad_D1.5mm; Rating bare copper pad; MPN PCB test pad D1.5mm
U3: BQ24074RGTR; VQFN-16-1EP_3x3mm_P0.5mm_EP1.6x1.6mm; Rating IN 4.35-10.5V op (26V no-damage), OUT r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; MPN BQ24074RGTR
U4: TPS62A01QDRLRQ1; SOT-563; Rating 2.5-5.5V in, 1A, AEC-Q100 grade 1 (SLUS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; MPN TPS62A01QDRLRQ1

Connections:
+3V3: C25.1, C26.1, L2.2, R23.2, R24.2, R25.2, R30.1, TP8.1; also elsewhere on the board
/3_Battery_3V3/BAT_TS: C23.1, J3.2, R28.1, U3.1 (TS)
/3_Battery_3V3/BQ_CE: R22.1, R23.1, U3.4 (~CE)
/3_Battery_3V3/BQ_ILIM: R21.1, U3.12 (ILIM)
/3_Battery_3V3/BQ_ISET: R20.1, U3.16 (ISET)
/3_Battery_3V3/BUCK3_FB: C26.2, R30.2, R31.1, U4.5 (FB)
/3_Battery_3V3/BUCK3_SW: L2.1, U4.2 (SW)
/3_Battery_3V3/LED_CHG_A: D2.2 (A), R26.2
/3_Battery_3V3/VBAT: C22.1, R27.2, TP5.1, U3.2 (BAT), U3.3 (BAT)
/3_Battery_3V3/VBATSYS: C21.1, C24.1, R26.1, TP6.1, U3.5 (EN2), U3.10 (OUT), U3.11 (OUT), U4.3 (VIN), U4.4 (EN)
/3_Battery_3V3/VBAT_CONN: J3.1, R27.1
BQ_PGOOD: R24.1, U3.7 (~PGOOD); also elsewhere on the board
BQ_nCHG: D2.1 (K), R25.1, TP7.1, U3.9 (~CHG); also elsewhere on the board
GND: C20.2, C21.2, C22.2, C23.2, C24.2, C25.2, J3.3, R20.2, R21.2, R22.2, R28.2, R31.2, U3.6 (EN1), U3.8 (VSS), U3.17 (EP), U4.1 (GND); also elsewhere on the board
V6P0: C20.1, U3.13 (IN); also elsewhere on the board

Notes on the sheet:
Power-path behaviour (TI BQ24074 SLUS810N): V6P0 present: OUT regulated to 4.4V, battery charged at 100mA (ILIM 0.5A total). V6P0 lost: OUT connects to VBAT with no glitch; TPS62A01 keeps +3V3 up -> BLE/MCU keep running; TCAN4550 loses VSUP (bus off) and is held in reset by MCU.
Backup battery: charger + power path
3V3 loads (typ/max): CC2340 ~7mA TX/RX / 12mA; TCAN VIO 3mA (crystal); LEDs ~2mA -> < 60mA. TPS62A01 1A capable; large margin. Output cap 22uF (matrix ++ in datasheet Table 8-3).
3.3 V logic rail
